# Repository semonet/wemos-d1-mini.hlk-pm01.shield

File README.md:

# NEW! Can be ordered at the pcbway.com link below for about 1$ a piece + shipping. Enjoy!

# AC power shield for Wemos D1 Mini (HLK-PM01)

## What does it do?
The [HLK-PM01](http://www.hlktech.net/product_detail.php?ProId=54) is a single module AC-DC converter, converting 100VAC / 240VAC to 5VDC.

This is simply a shield, which fits the module in order to power the Wemos D1 Mini directly from AC power lines.

## What does it look like (PCB)?

## What does it look like (3D)?

# Attribution

## Wemos D1 Mini Shield
Found in: `lib/D1_mini.pretty/`

Based on the shields template for [Wemos D1 Mini by Jérôme Labidurie.](https://github.com/jerome-labidurie/d1_mini_kicad)

## HLK-PM01
Found in: `lib/Power_Supplies*`, `lib/Power_Supply/` and `lib/Power_Supply.pretty/`

HLK-PM01 model pulled from [CascoLogix KiCAD Libraries](https://github.com/CascoLogix/KiCAD_Libraries)

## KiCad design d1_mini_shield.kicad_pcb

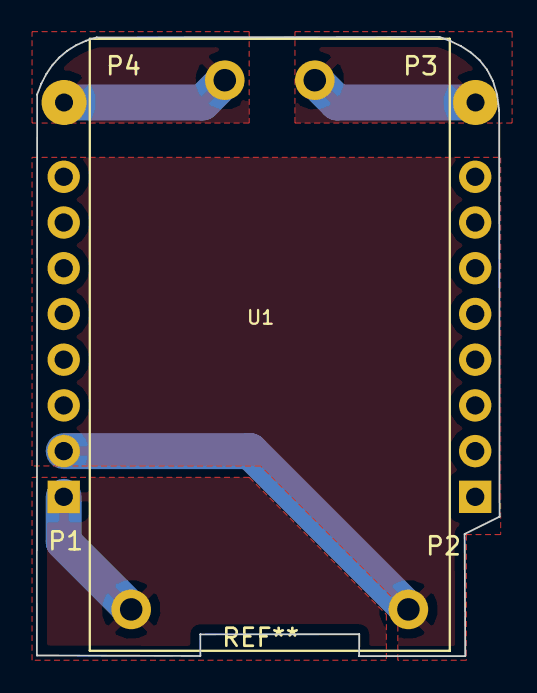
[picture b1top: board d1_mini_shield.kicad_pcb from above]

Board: 2 copper layers, 25.7 x 34.4 mm, 5 parts (0 on the bottom side), 4 nets.

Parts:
P1, P2: CONN_01X08; D1_mini_Pin_Header
P3, P4: CONN_01X01; SolderWirePad_single_1mmDrill
U1: HLK-PM05; HLK-PM01

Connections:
/+5V: P1.1, U1.4
/GND: P1.2, U1.3
unnamed: P3.1, U1.1
unnamed: P4.1, U1.2

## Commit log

2017-08-25 Fixed broken images
2017-08-25 gitignore file!
2017-08-25 Committed content
